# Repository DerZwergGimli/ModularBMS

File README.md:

## Battery Management System [BMS]

This is a Bachelor Project made at the HTWG.

This Project is about a Battery Management System - build as a scale-able system.

## Boards

### Master

#### - Battery Management System [BMS]

### Slaves

#### - Battery Monitoring Unit [BMU]

#### - Battery Junction Box [BJB]

### Extra

#### - 6 Cell Battery Simulator [6CBS]

### 

### 

### 

###

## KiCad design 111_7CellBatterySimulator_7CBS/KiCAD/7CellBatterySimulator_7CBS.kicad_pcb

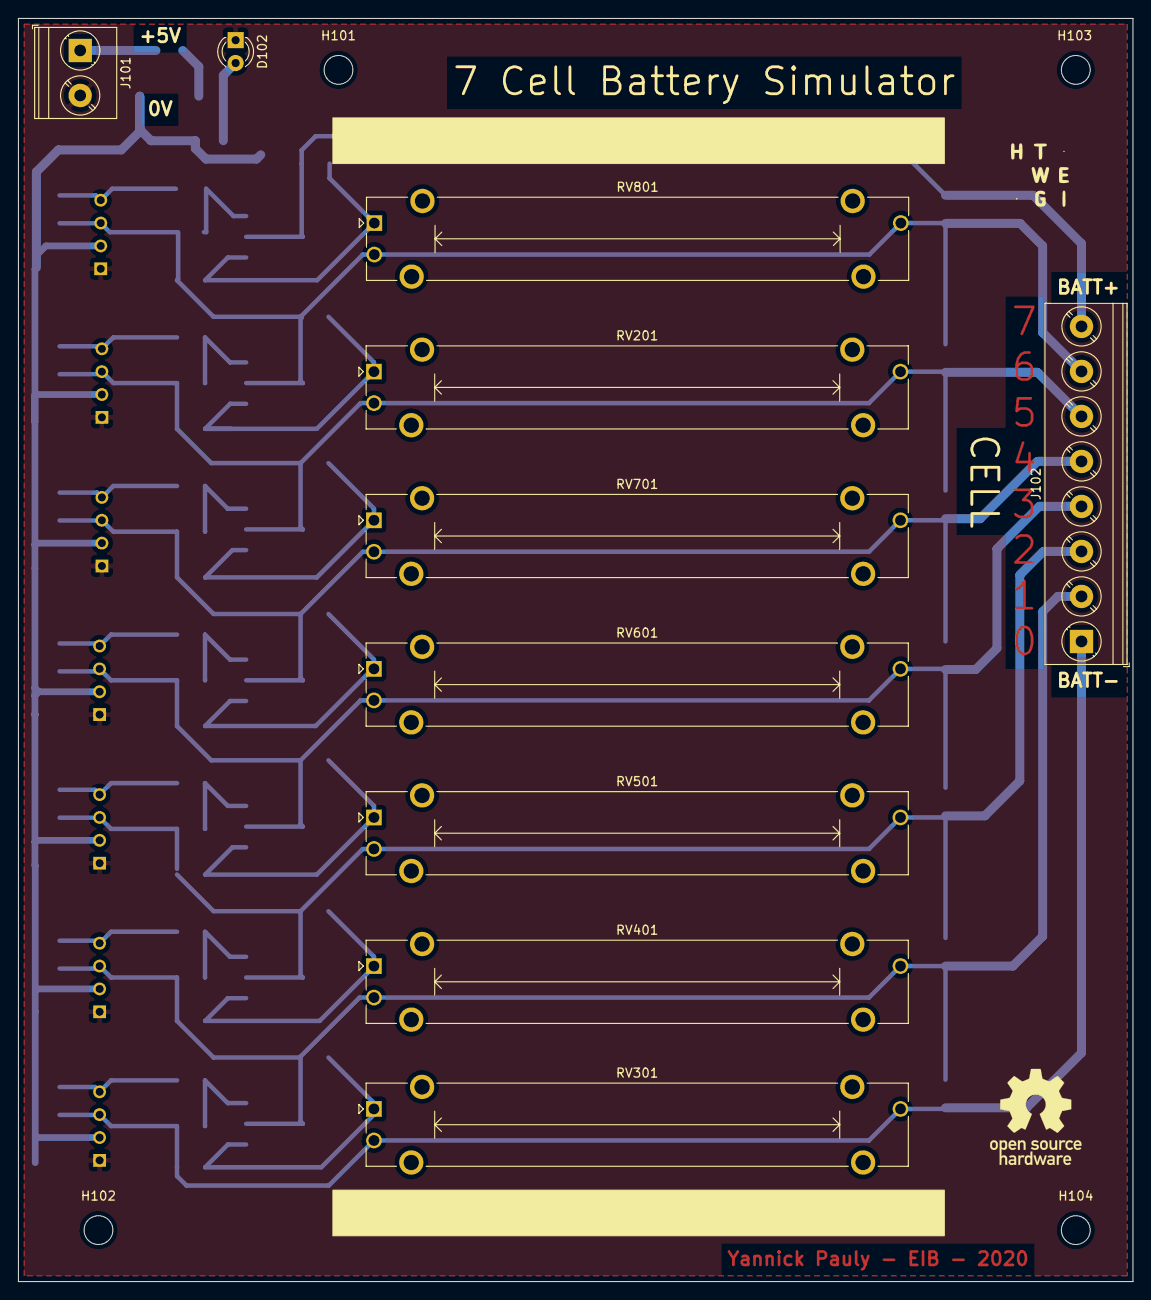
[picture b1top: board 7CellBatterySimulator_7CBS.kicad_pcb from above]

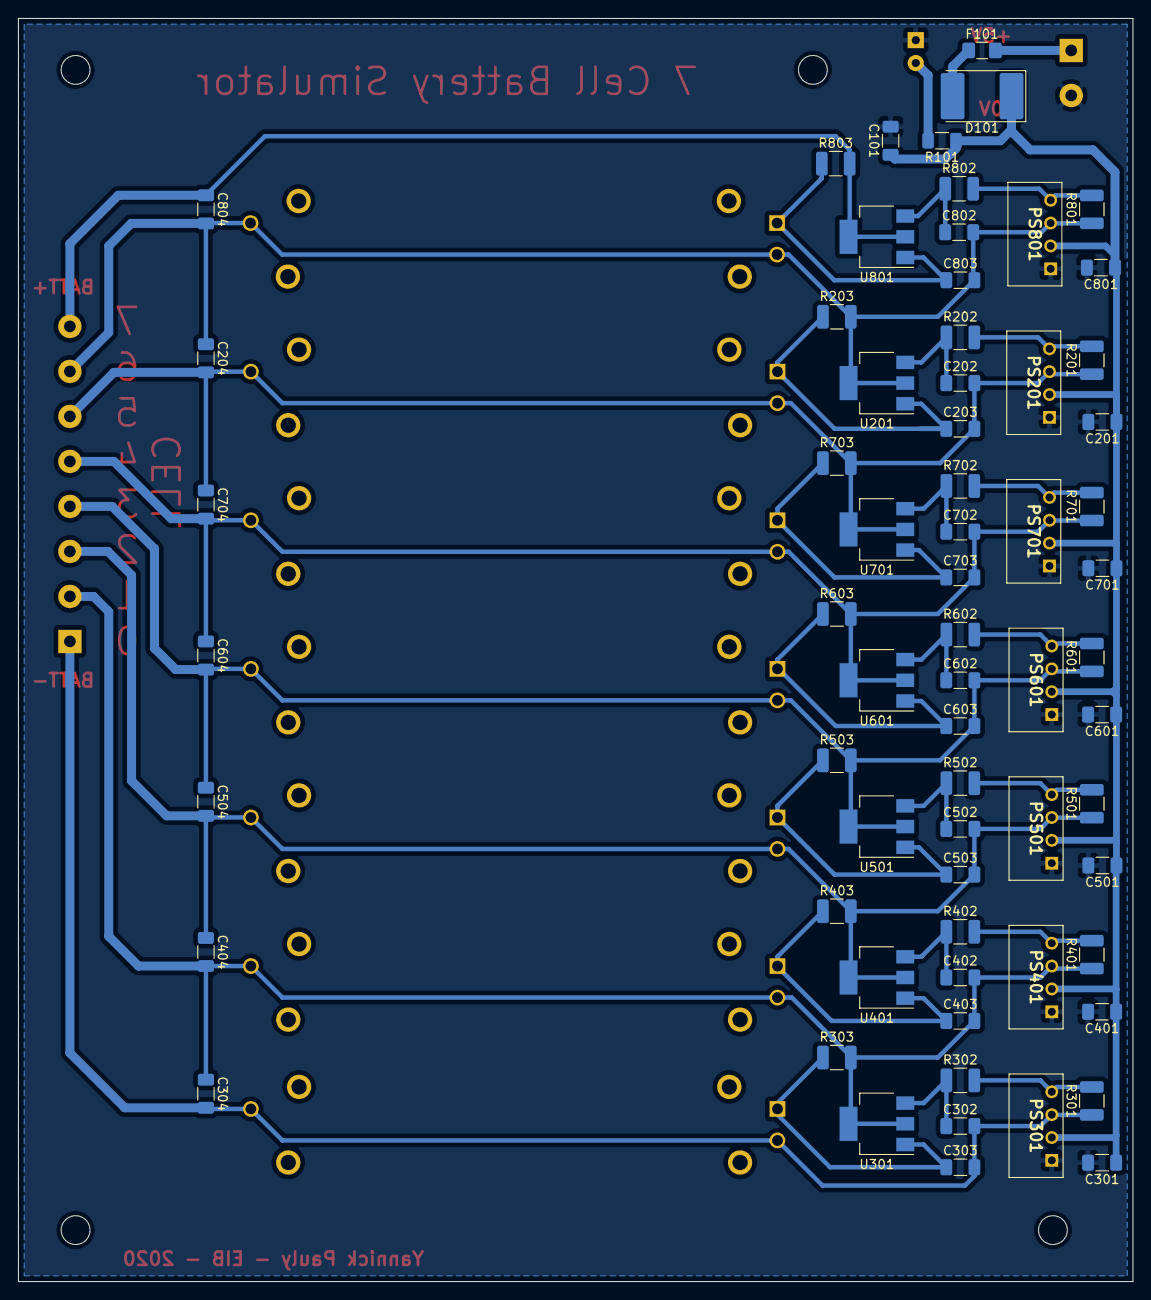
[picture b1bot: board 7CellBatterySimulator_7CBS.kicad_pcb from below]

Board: 2 copper layers, 123.8 x 140.3 mm, 83 parts (67 on the bottom side), 34 nets.

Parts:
C101: 47u; C_1206_3216Metric_Pad1.33x1.80mm_HandSolder
C201, C301, C401, C501, C601, C701, C801: 10u*; C_1206_3216Metric_Pad1.33x1.80mm_HandSolder
C202, C302, C402, C502, C602, C702, C802: 0.1u*; C_1206_3216Metric_Pad1.33x1.80mm_HandSolder
C203, C303, C403, C503, C603, C703, C803: 1u*; C_1206_3216Metric_Pad1.33x1.80mm_HandSolder
C204, C304, C404, C504, C604, C704, C804: 100u; C_1206_3216Metric_Pad1.33x1.80mm_HandSolder
D101: 60V; D_3220_8050Metric_Pad2.65x5.15mm_HandSolder
D102: LED; LED_D3.0mm
F101: 4A; Fuse_1206_3216Metric_Pad1.42x1.75mm_HandSolder
H101, H102, H103, H104: MountingHole; MountingHole_3.2mm_M3_DIN965
J101: Screw_Terminal_01x02; TerminalBlock_Phoenix_PT-1,5-2-5.0-H_1x02_P5.00mm_Horizontal
J102: Screw_Terminal_01x08; TerminalBlock_Phoenix_PT-1,5-8-5.0-H_1x08_P5.00mm_Horizontal
L101: LogoHTWG; HTWG_LOGO
L102: LogoOSH; OpenSouceHardwareLOGO
PS201, PS301, PS401, PS501, PS601, PS701, PS801: ROE-0512S; ROE1205S
R101: 330; R_1206_3216Metric_Pad1.30x1.75mm_HandSolder
R201, R301, R401, R501, R601, R701, R801: 1k, DNP; R_1210_3225Metric_Pad1.30x2.65mm_HandSolder
R202, R302, R402, R502, R602, R702, R802: 22; R_1210_3225Metric_Pad1.30x2.65mm_HandSolder
R203, R303, R403, R503, R603, R703, R803: 380; R_1210_3225Metric_Pad1.30x2.65mm_HandSolder
RV201, RV301, RV401, RV501, RV601, RV701, RV801: 1k; Potentiometer_Bourns_PTA4543_Single_Slide
U201, U301, U401, U501, U601, U701, U801: LM317_SOT-223; SOT-223-3_TabPin2

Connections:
+5V: C101.1, C201.1, C301.1, C401.1, C501.1, C601.1, C701.1, C801.1, D101.1, PS201.2, PS301.2, PS401.2, PS501.2, PS601.2, PS701.2, PS801.2, R101.1
/Channel1/OUT+: C304.1, C402.2, C403.2, C404.2, J102.2, PS401.3, R303.2, R401.1, RV401.2, RV401.3, U301.2
/Channel1/OUT-: C302.2, C303.2, C304.2, J102.1, PS301.3, R301.1, RV301.2, RV301.3
/Channel2/OUT+: C404.1, C502.2, C503.2, C504.2, J102.3, PS501.3, R403.2, R501.1, RV501.2, RV501.3, U401.2
/Channel3/OUT+: C504.1, C602.2, C603.2, C604.2, J102.4, PS601.3, R503.2, R601.1, RV601.2, RV601.3, U501.2
/Channel4/OUT+: C604.1, C702.2, C703.2, C704.2, J102.5, PS701.3, R603.2, R701.1, RV701.2, RV701.3, U601.2
/Channel5/OUT+: C202.2, C203.2, C204.2, C704.1, J102.6, PS201.3, R201.1, R703.2, RV201.2, RV201.3, U701.2
/Channel6/OUT+: C204.1, C802.2, C803.2, C804.2, J102.7, PS801.3, R203.2, R801.1, RV801.2, RV801.3, U201.2
/Channel7/OUT+: C804.1, J102.8, R803.2, U801.2
GND: C101.2, C201.2, C301.2, C401.2, C501.2, C601.2, C701.2, C801.2, D102.1, J101.2, PS201.1, PS301.1, PS401.1, PS501.1, PS601.1, PS701.1, PS801.1
unnamed: C202.1, R202.1, U201.3
unnamed: C203.1, R203.1, RV201.1, U201.1
unnamed: C302.1, R302.1, U301.3
unnamed: C303.1, R303.1, RV301.1, U301.1
unnamed: C402.1, R402.1, U401.3
unnamed: C403.1, R403.1, RV401.1, U401.1
unnamed: C502.1, R502.1, U501.3
unnamed: C503.1, R503.1, RV501.1, U501.1
unnamed: C602.1, R602.1, U601.3
unnamed: C603.1, R603.1, RV601.1, U601.1
unnamed: C702.1, R702.1, U701.3
unnamed: C703.1, R703.1, RV701.1, U701.1
unnamed: C802.1, R802.1, U801.3
unnamed: C803.1, R803.1, RV801.1, U801.1
unnamed: D101.2, F101.1
unnamed: D102.2, R101.2
unnamed: F101.2, J101.1
unnamed: PS201.4, R201.2, R202.2
unnamed: PS301.4, R301.2, R302.2
unnamed: PS401.4, R401.2, R402.2
unnamed: PS501.4, R501.2, R502.2
unnamed: PS601.4, R601.2, R602.2
unnamed: PS701.4, R701.2, R702.2
unnamed: PS801.4, R801.2, R802.2

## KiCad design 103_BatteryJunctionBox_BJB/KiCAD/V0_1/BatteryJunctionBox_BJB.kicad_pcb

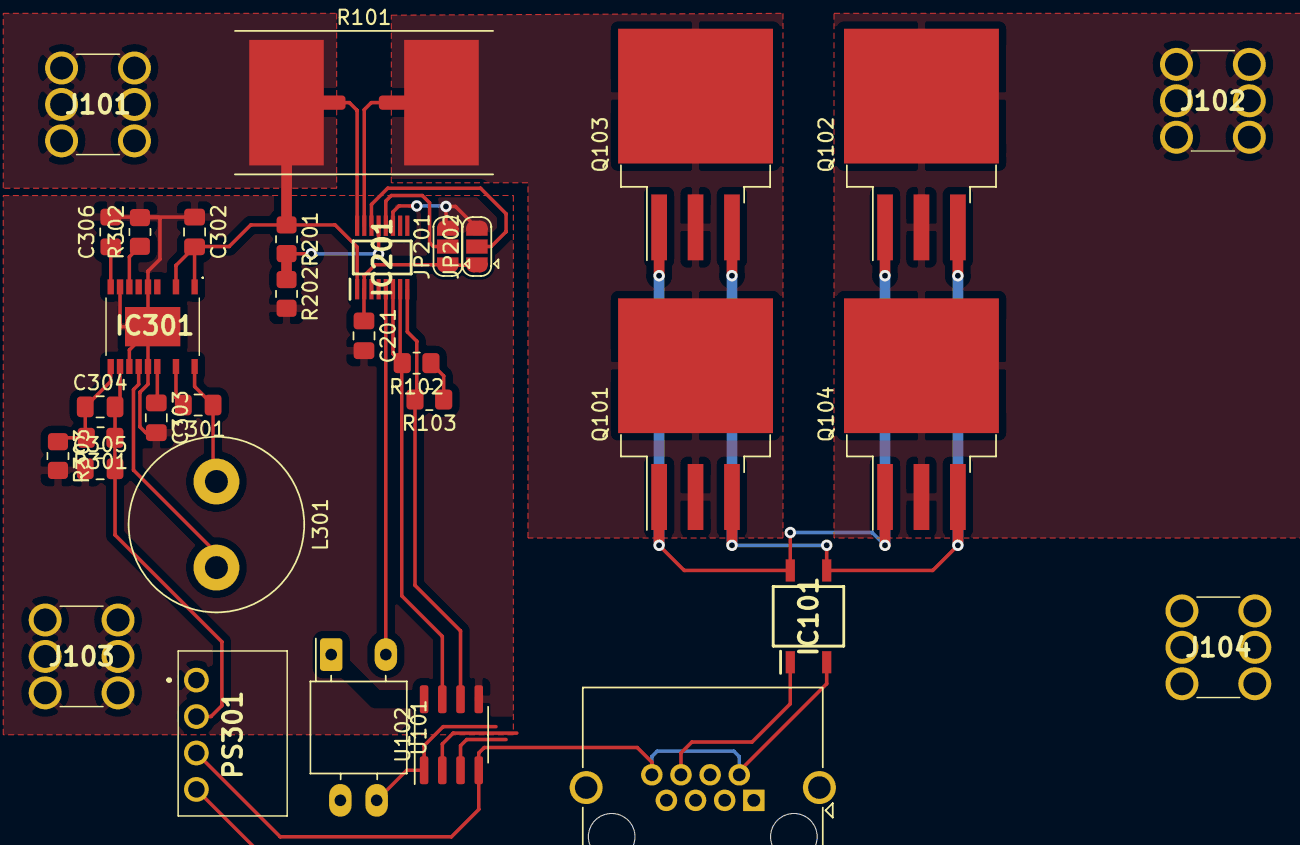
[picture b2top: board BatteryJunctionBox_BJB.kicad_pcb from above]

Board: 2 copper layers, 33 parts (0 on the bottom side), 30 nets.

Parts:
C201, C301, C306: 0.1u; C_0805_2012Metric_Pad1.18x1.45mm_HandSolder
C302, C303: 2.2u; C_0805_2012Metric_Pad1.18x1.45mm_HandSolder
C304: 10p; C_0805_2012Metric_Pad1.18x1.45mm_HandSolder
C305: 47u; C_0805_2012Metric_Pad1.18x1.45mm_HandSolder
IC101: VOM1271T; SOP-4
IC201: LTC2946; MSOP_16_Lead_Plastic
IC301: LT8630IFE#PBF; LT8630IFEPBF
J101, J102, J103, J104: WuertHA_7461057
J105: RJ45_Shielded; RJ45_Amphenol_RJHSE5380
JP201, JP202: Jumper_3_Open; SolderJumper-3_P1.3mm_Open_RoundedPad1.0x1.5mm
L301: 22u; L_Radial_D12.0mm_P6.00mm_MuRATA_1900R
PS301: RI-1205S; SIP4_SingleOutput
Q101, Q102, Q103, Q104: Q_NMOS_GDS; TO-263-3_TabPin2
R101: 0.001; R_Shunt_16x8-75_Bourns_4Pin
R102, R103: 10k; R_0805_2012Metric_Pad1.20x1.40mm_HandSolder
R201, R301: 1Mega; R_0805_2012Metric_Pad1.20x1.40mm_HandSolder
R202: 20k; R_0805_2012Metric_Pad1.20x1.40mm_HandSolder
R302: 8.66k; R_0805_2012Metric_Pad1.20x1.40mm_HandSolder
R303: 71.5k; R_0805_2012Metric_Pad1.20x1.40mm_HandSolder
U101: NSL-32; Luna_NSL-32
U102: ISO1541; SOIC-8_3.9x4.9mm_P1.27mm

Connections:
+3V3: J105.7, U101.3, U102.1
+5V: C201.1, IC201.2, JP201.1, JP202.1, R102.1, R103.1, U101.1, U102.8
+BATT: C302.2, IC201.1, IC301.1, IC301.3, J101.1, J101.2, J101.3, J101.4, J101.5, J101.6, R101.1, R201.1
-BATT: C201.2, C302.1, C303.2, C305.1, C306.2, IC201.11, IC301.6, IC301.9, IC301.13, IC301.15, IC301.21, J103.1, J103.2, J103.3, J103.4, J103.5, J103.6, J104.1, J104.2, J104.3, J104.4, J104.5, J104.6, JP201.3, JP202.3, PS301.1, R202.2, R302.2, R303.2, U102.5
/IsoPowerSupply/12V_OUT: C304.2, C305.2, IC301.12, PS301.2, R301.1
/PowerMonitor/ADIN: IC201.13, R201.2, R202.1
/PowerMonitor/Address0: IC201.12, JP201.2
/PowerMonitor/Address1: IC201.14, JP202.2
I2C_SCL: IC201.8, R103.2, U102.6
I2C_SCL_ISO: J105.4, U102.3
I2C_SDA: IC201.6, IC201.7, R102.2, U102.7
I2C_SDA_ISO: J105.3, U102.2
ISO_+5V: J105.1, PS301.4
ISO_GND: IC101.2, J105.2, J105.8, PS301.3, U102.4
Interrupt_NO: J105.5, U101.4
MOSFET_G: IC101.4, Q101.1, Q102.1, Q103.1, Q104.1
MOSFET_S: IC101.3, Q101.3, Q102.3, Q103.3, Q104.3
MOSFET_SWITCH: IC101.1, J105.6
unnamed: C301.1, IC301.20, L301.1
unnamed: C301.2, IC301.18
unnamed: C303.1, IC301.16
unnamed: C304.1, IC301.11, R301.2, R303.1
unnamed: C306.1, IC301.10
unnamed: IC301.8, R302.1
unnamed: IC301.14, L301.2
unnamed: J102.1, J102.2, J102.3, J102.4, J102.5, J102.6, Q102.2, Q104.2
unnamed: Q101.2, Q103.2, R101.4
SHUNT+: IC201.16, R101.2
SHUNT-: IC201.15, R101.3
~ALERT: IC201.5, U101.2

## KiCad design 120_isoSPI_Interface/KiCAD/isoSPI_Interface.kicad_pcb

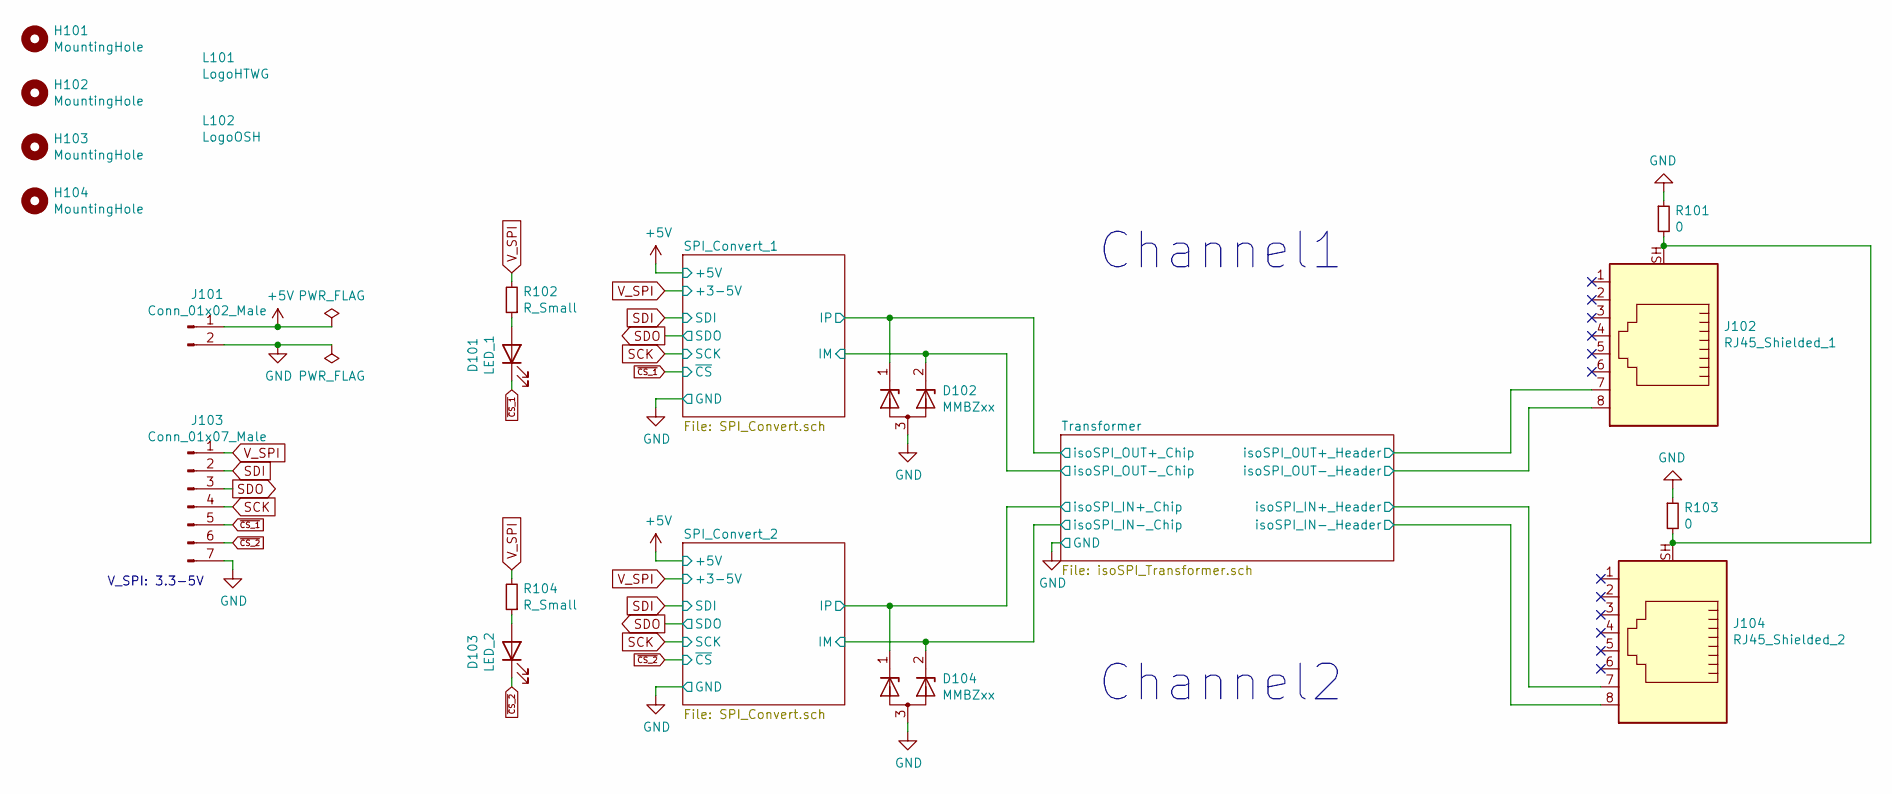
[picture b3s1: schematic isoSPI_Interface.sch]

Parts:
D101: LED_1; LED_D3.0mm
D102, D104: MMBZxx; SOT-23
D103: LED_2; LED_D3.0mm
H101, H102, H103, H104: MountingHole; MountingHole_3.2mm_M3_DIN965
J101: Conn_01x02_Male; PinHeader_1x02_P2.54mm_Vertical
J102: RJ45_Shielded_1; RJ45_Amphenol_RJHSE5380
J103: Conn_01x07_Male; PinHeader_1x07_P2.54mm_Vertical
J104: RJ45_Shielded_2; RJ45_Amphenol_RJHSE5380
L101: LogoHTWG; HTWG_LOGO
L102: LogoOSH; OpenSouceHardwareLOGO
R101, R103: 0; R_0805_2012Metric_Pad1.20x1.40mm_HandSolder
R102, R104: R_Small; R_0805_2012Metric_Pad1.20x1.40mm_HandSolder

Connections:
+5V: J101.1; also elsewhere on the board
/SPI_Convert_1/IM: D102.2 (K); also elsewhere on the board
/SPI_Convert_1/IP: D102.1 (K); also elsewhere on the board
/SPI_Convert_2/IM: D104.2 (K); also elsewhere on the board
/SPI_Convert_2/IP: D104.1 (K); also elsewhere on the board
/Transformer/isoSPI_IN+_Header: J104.7; also elsewhere on the board
/Transformer/isoSPI_IN-_Header: J104.8; also elsewhere on the board
/Transformer/isoSPI_OUT+_Header: J102.7; also elsewhere on the board
/Transformer/isoSPI_OUT-_Header: J102.8; also elsewhere on the board
GND: D102.3 (A), D104.3 (A), J101.2, J103.7, R101.1, R103.1; also elsewhere on the board
unnamed: D101.2 (A), R102.1
unnamed: D103.2 (A), R104.1
unnamed: J102.SH, J104.SH, R101.2, R103.2
SCK: J103.4; also elsewhere on the board
SDI: J103.2; also elsewhere on the board
SDO: J103.3; also elsewhere on the board
V_SPI: J103.1, R102.2, R104.2; also elsewhere on the board
~CS_1: D101.1 (K), J103.5; also elsewhere on the board
~CS_2: D103.1 (K), J103.6; also elsewhere on the board

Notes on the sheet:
V_SPI: 3.3-5V
Channel1
Channel2

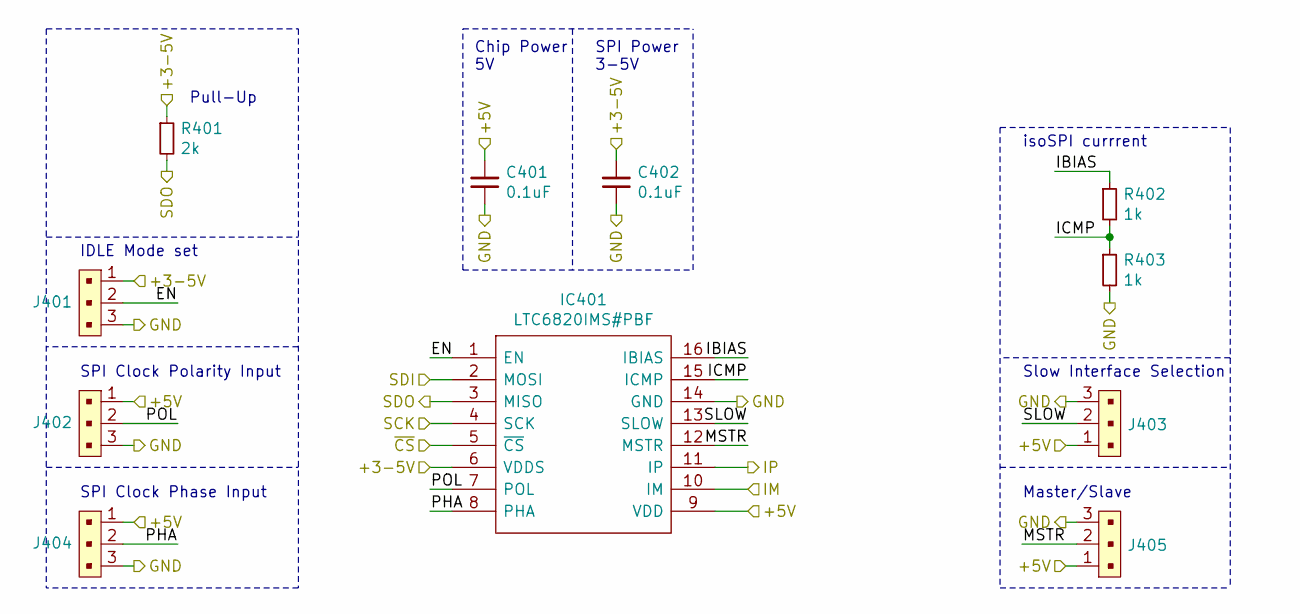
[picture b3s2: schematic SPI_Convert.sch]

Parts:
C201, C202: 0.1uF; C_0805_2012Metric_Pad1.18x1.45mm_HandSolder
IC201: LTC6820IMS#PBF; MSOP-16_3x4.039mm_P0.5mm
J201, J202, J203, J204, J205: 3PinHeader; PinHeader_1x03_P2.54mm_Vertical; MPN 640456-3; Digi-Key_PN A19470-ND
R201: 2k; R_0805_2012Metric_Pad1.20x1.40mm_HandSolder
R202, R203: 1k; R_0805_2012Metric_Pad1.20x1.40mm_HandSolder

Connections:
+5V: C201.2, IC201.9 (VDD), J202.1, J203.1, J204.1, J205.1; also elsewhere on the board
/SPI_Convert_1/EN: IC201.1 (EN), J201.2
/SPI_Convert_1/IBIAS: IC201.16 (IBIAS), R202.1
/SPI_Convert_1/ICMP: IC201.15 (ICMP), R202.2, R203.1
/SPI_Convert_1/IM: IC201.10 (IM); also elsewhere on the board
/SPI_Convert_1/IP: IC201.11 (IP); also elsewhere on the board
/SPI_Convert_1/MSTR: IC201.12 (MSTR), J205.2
/SPI_Convert_1/PHA: IC201.8 (PHA), J204.2
/SPI_Convert_1/POL: IC201.7 (POL), J202.2
/SPI_Convert_1/SLOW: IC201.13 (SLOW), J203.2
GND: C201.1, C202.1, IC201.14 (GND), J201.3, J202.3, J203.3, J204.3, J205.3, R203.2; also elsewhere on the board
SCK: IC201.4 (SCK); also elsewhere on the board
SDI: IC201.2 (MOSI); also elsewhere on the board
SDO: IC201.3 (MISO), R201.2; also elsewhere on the board
V_SPI: C202.2, IC201.6 (VDDS), J201.1, R201.1; also elsewhere on the board
~CS_1: IC201.5 (~CS); also elsewhere on the board

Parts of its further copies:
C401, C402: 0.1uF; C_0805_2012Metric_Pad1.18x1.45mm_HandSolder
IC401: LTC6820IMS#PBF; MSOP-16_3x4.039mm_P0.5mm
J401, J402, J403, J404, J405: 3PinHeader; PinHeader_1x03_P2.54mm_Vertical; MPN 640456-3; Digi-Key_PN A19470-ND
R401: 2k; R_0805_2012Metric_Pad1.20x1.40mm_HandSolder
R402, R403: 1k; R_0805_2012Metric_Pad1.20x1.40mm_HandSolder

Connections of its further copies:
+5V: C401.2, IC401.9 (VDD), J402.1, J403.1, J404.1, J405.1; also elsewhere on the board
/SPI_Convert_2/EN: IC401.1 (EN), J401.2
/SPI_Convert_2/IBIAS: IC401.16 (IBIAS), R402.1
/SPI_Convert_2/ICMP: IC401.15 (ICMP), R402.2, R403.1
/SPI_Convert_2/IM: IC401.10 (IM); also elsewhere on the board
/SPI_Convert_2/IP: IC401.11 (IP); also elsewhere on the board
/SPI_Convert_2/MSTR: IC401.12 (MSTR), J405.2
/SPI_Convert_2/PHA: IC401.8 (PHA), J404.2
/SPI_Convert_2/POL: IC401.7 (POL), J402.2
/SPI_Convert_2/SLOW: IC401.13 (SLOW), J403.2
GND: C401.1, C402.1, IC401.14 (GND), J401.3, J402.3, J403.3, J404.3, J405.3, R403.2; also elsewhere on the board
SCK: IC401.4 (SCK); also elsewhere on the board
SDI: IC401.2 (MOSI); also elsewhere on the board
SDO: IC401.3 (MISO), R401.2; also elsewhere on the board
V_SPI: C402.2, IC401.6 (VDDS), J401.1, R401.1; also elsewhere on the board
~CS_2: IC401.5 (~CS); also elsewhere on the board

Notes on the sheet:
Master/Slave
Slow Interface Selection
Chip Power 5V
SPI Power 3-5V
SPI Clock Polarity Input
SPI Clock Phase Input
IDLE Mode set
Pull-Up
isoSPI currrent

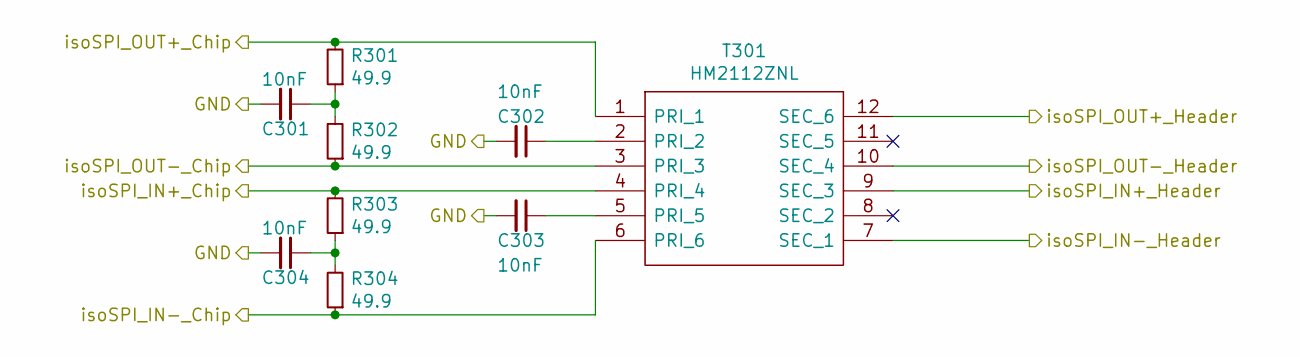
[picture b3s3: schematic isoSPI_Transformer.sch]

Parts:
C301, C302, C303, C304: 10nF; C_0805_2012Metric_Pad1.18x1.45mm_HandSolder
R301, R302, R303, R304: 49.9; R_0805_2012Metric_Pad1.20x1.40mm_HandSolder
T301: HM2112ZNL; SOP200P1543X320-12N; Manufacturer_Part_Number HM2112ZNL; Mouser Part Number 673-HM2112ZNL

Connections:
/SPI_Convert_1/IM: R302.1, T301.3 (PRI_3); also elsewhere on the board
/SPI_Convert_1/IP: R301.2, T301.1 (PRI_1); also elsewhere on the board
/SPI_Convert_2/IM: R304.1, T301.6 (PRI_6); also elsewhere on the board
/SPI_Convert_2/IP: R303.2, T301.4 (PRI_4); also elsewhere on the board
/Transformer/isoSPI_IN+_Header: T301.9 (SEC_3); also elsewhere on the board
/Transformer/isoSPI_IN-_Header: T301.7 (SEC_1); also elsewhere on the board
/Transformer/isoSPI_OUT+_Header: T301.12 (SEC_6); also elsewhere on the board
/Transformer/isoSPI_OUT-_Header: T301.10 (SEC_4); also elsewhere on the board
GND: C301.2, C302.2, C303.2, C304.2; also elsewhere on the board
unnamed: C301.1, R301.1, R302.2
unnamed: C302.1, T301.2 (PRI_2)
unnamed: C303.1, T301.5 (PRI_5)
unnamed: C304.1, R303.1, R304.2

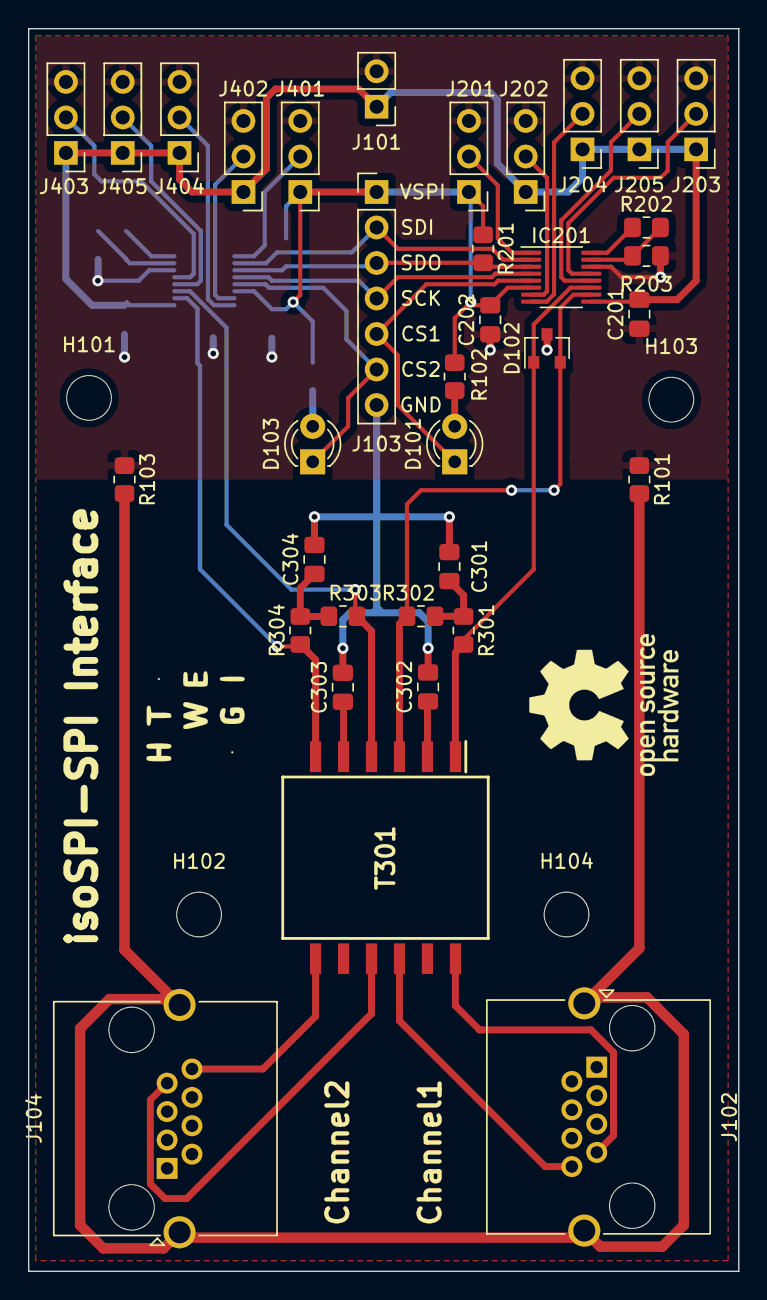
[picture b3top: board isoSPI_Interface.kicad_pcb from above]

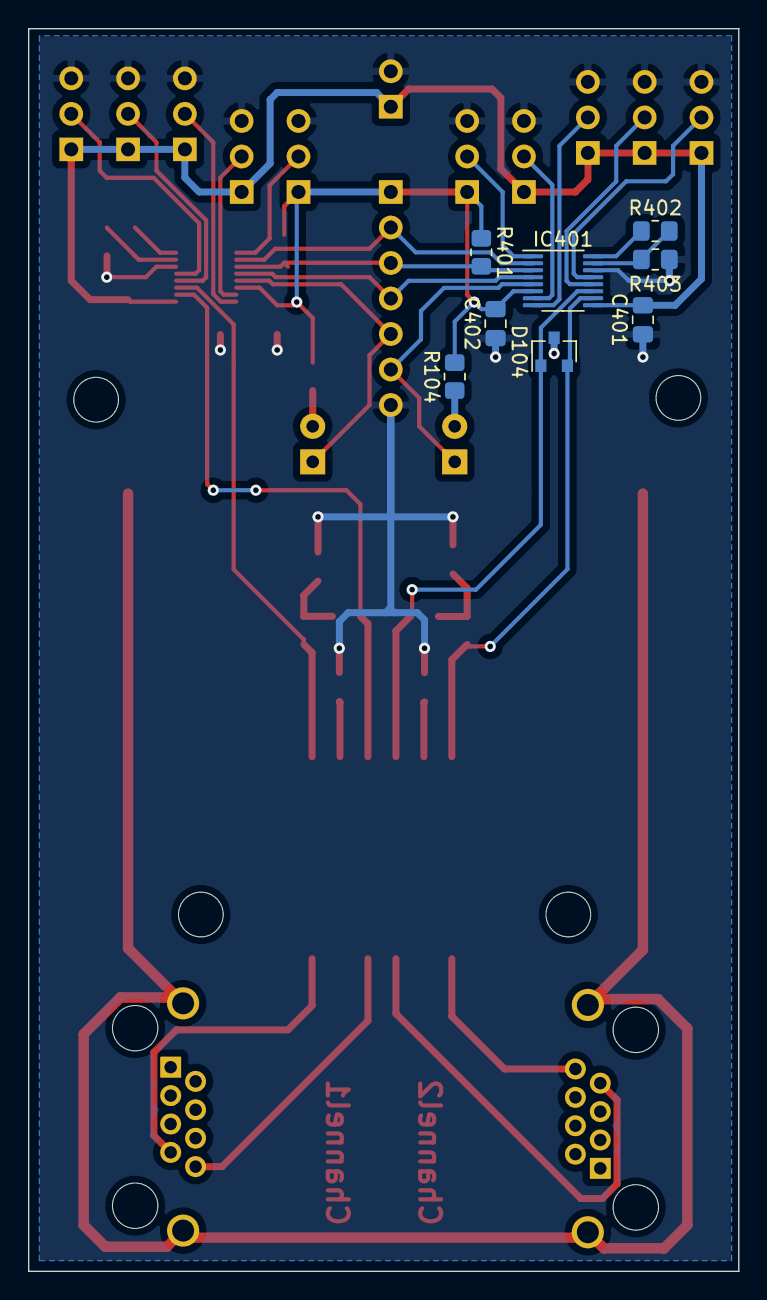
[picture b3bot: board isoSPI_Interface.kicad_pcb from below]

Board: 2 copper layers, 50.8 x 88.9 mm, 49 parts (8 on the bottom side), 37 nets.

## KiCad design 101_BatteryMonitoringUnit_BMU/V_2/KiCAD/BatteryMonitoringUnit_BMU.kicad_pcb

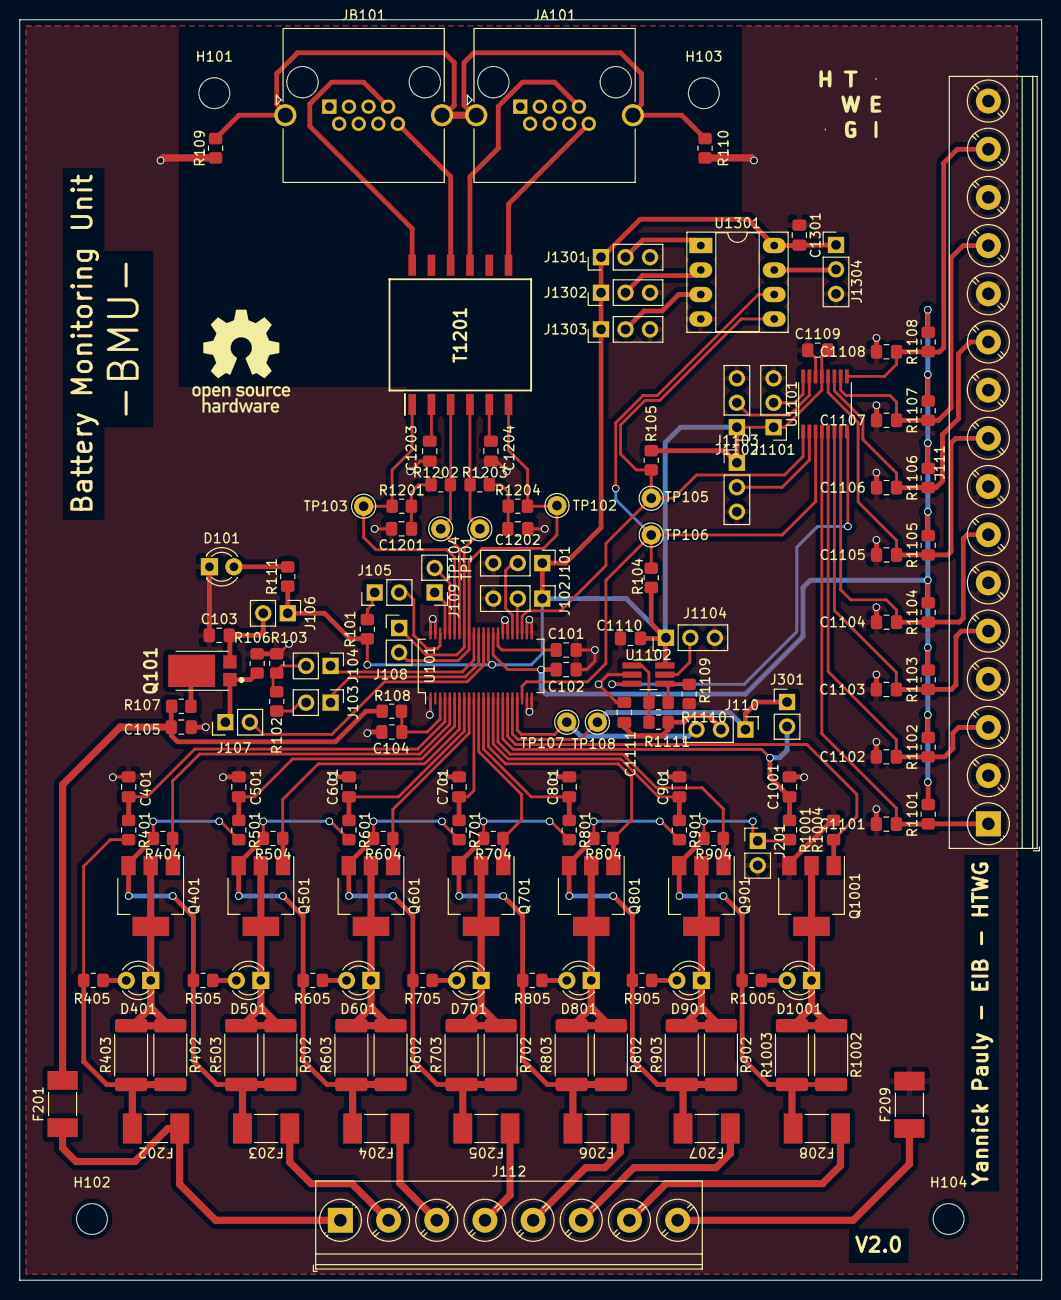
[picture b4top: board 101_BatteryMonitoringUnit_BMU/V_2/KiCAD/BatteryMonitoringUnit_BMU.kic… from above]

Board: 2 copper layers, 106.0 x 130.8 mm, 157 parts (0 on the bottom side), 101 nets.

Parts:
C101, C102, C103: 1uF; C_0805_2012Metric_Pad1.18x1.45mm_HandSolder
C104, C1111, C1201, C1202, C1203, C1204: 10nF; C_0805_2012Metric_Pad1.18x1.45mm_HandSolder
C105, C1110: 0.1u; C_0805_2012Metric_Pad1.18x1.45mm_HandSolder
C401, C501, C601, C701, C801, C901, C1001: 10nF/30V; C_0805_2012Metric_Pad1.18x1.45mm_HandSolder
C1101, C1102, C1103, C1104, C1105, C1106, C1107, C1108: 10nF*; C_0805_2012Metric_Pad1.18x1.45mm_HandSolder
C1109, C1301: 100nF; C_0805_2012Metric_Pad1.18x1.45mm_HandSolder
D101: LED_Status; LED_D3.0mm
D401, D501, D601, D701, D801, D901, D1001: LED_Dis; LED_D3.0mm
F201, F209: Fuse_0.5A; Fuse_Littelfuse-NANO2-451_453
F202, F203, F204, F205, F206, F207, F208: Fuse_0.25A; Fuse_Littelfuse-NANO2-451_453
H101, H102, H103, H104: MountingHole; MountingHole_3.2mm_M3_DIN965
J101, J102, J110, J1101, J1102, J1103, J1104, J1301, J1302, J1303, J1304: 3PinHeader; PinHeader_1x03_P2.54mm_Vertical
J103, J104, J105, J106, J107, J108, J109, J201, J301: 2PinHeader; PinHeader_1x02_P2.54mm_Vertical
J111: TerminalBlock; TerminalBlock_Phoenix_PT-1,5-16-5.0-H_1x16_P5.00mm_Horizont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
J112: Screw_Terminal_01x08; TerminalBlock_Phoenix_PT-1,5-8-5.0-H_1x08_P5.00mm_Horizontal
JA101: RJ45; RJ45_Amphenol_RJHSE5380
JB101: RJ45; RJ45_Amphenol_RJHSE5380
L101: LogoHTWG; HTWG_LOGO
L102: LogoOSH; OpenSouceHardwareLOGO
Q101: DXT5551P5-13; DXT5551P513
Q401, Q501, Q601, Q701, Q801, Q901, Q1001: PZT2222A; SOT-223-3_TabPin2
R101: 1M; R_0805_2012Metric_Pad1.20x1.40mm_HandSolder
R102, R103, R404, R504, R604, R704, R804, R904, R1004: 1k; R_0805_2012Metric_Pad1.20x1.40mm_HandSolder
R104, R105, R1101, R1102, R1103, R1104, R1105, R1106, R1107, R1108, R1109: 10k; R_0805_2012Metric_Pad1.20x1.40mm_HandSolder
R106: 1k, DNP; R_0805_2012Metric_Pad1.20x1.40mm_HandSolder
R107, R109, R110, R1110: 0; R_0805_2012Metric_Pad1.20x1.40mm_HandSolder
R108: 10; R_0805_2012Metric_Pad1.20x1.40mm_HandSolder
R111, R405, R505, R605, R705, R805, R905, R1005: Rv_LED; R_0805_2012Metric_Pad1.20x1.40mm_HandSolder
R401, R501, R601, R701, R801, R901, R1001, R1111: 100; R_0805_2012Metric_Pad1.20x1.40mm_HandSolder
R402, R403, R502, R503, R602, R603, R702, R703, R802, R803, R902, R903, R1002, R1003: 100; R_2512_6332Metric_Pad1.40x3.35mm_HandSolder
R1201, R1202, R1203, R1204: 49.9; R_0805_2012Metric_Pad1.20x1.40mm_HandSolder
T1201: HM2112ZNL; SOP200P1543X320-12N
TP101, TP102, TP103, TP104, TP105, TP106, TP107, TP108: TestPoint; Pin_D1.0mm_L10.0mm
U101: LTC6810-1_mod; SSOP-44_5.3x12.8mm_P0.5mm
U1101: ADG728; TSSOP-16_4.4x5mm_P0.65mm
U1102: LTC6255; TSOT-23-6_HandSoldering
U1301: 24LC256; DIP-8_W7.62mm_Socket_LongPads

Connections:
+BATT: F201.1, F202.1, J112.1
+BATT_Fused: C105.2, F201.2, R107.1, R108.2
-BATT: F209.1, J112.8
-BATT_Fused: C101.2, C102.2, C103.1, C104.1, C105.1, C401.2, C501.2, C601.2, C701.2, C801.2, C901.2, C1001.2, C1101.2, C1102.2, C1103.2, C1104.2, C1105.2, C1106.2, C1107.2, C1108.2, C1109.1, C1110.2, C1111.2, C1201.2, C1202.2, C1203.2, C1204.1, C1301.1, D101.1, F209.2, J101.3, J102.3, J111.2, J111.4, J111.6, J111.8, J111.10, J111.12, J111.14, J111.16, J201.2, J1101.3, J1102.3, J1103.3, J1104.3, J1301.3, J1302.3, J1303.3, J1304.3, Q1001.3, R103.1, R106.2, R109.1, R110.1, R1004.2, R1109.2, U101.1, U101.21, U101.22, U101.23, U101.24, U101.28, U101.29, U101.43, U101.44, U1101.14, U1102.2, U1301.4
/+Cell_0: F208.1, J112.7
/+Cell_1: F207.1, J112.6
/+Cell_2: F206.1, J112.5
/+Cell_3: F205.1, J112.4
/+Cell_4: F204.1, J112.3
/+Cell_5: F203.1, J112.2
/BalanceFuses/+FusedCell_0: F208.2, J201.1, Q901.3, R904.2, R1001.2, R1002.2, R1003.1, R1005.1
/BalanceFuses/+FusedCell_1: F207.2, Q801.3, R804.2, R901.2, R902.2, R903.1, R905.1
/BalanceFuses/+FusedCell_2: F206.2, Q701.3, R704.2, R801.2, R802.2, R803.1, R805.1
/BalanceFuses/+FusedCell_3: F205.2, Q601.3, R604.2, R701.2, R702.2, R703.1, R705.1
/BalanceFuses/+FusedCell_4: F204.2, Q501.3, R504.2, R601.2, R602.2, R603.1, R605.1
/BalanceFuses/+FusedCell_5: F203.2, Q401.3, R404.2, R501.2, R502.2, R503.1, R505.1
/BalanceFuses/+FusedCell_6: F202.2, R401.2, R402.2, R403.1, R405.1
/C_0: C1001.1, J301.2, R1001.1, U101.16
/C_1: C901.1, R901.1, U101.14
/C_2: C801.1, R801.1, U101.12
/C_3: C701.1, R701.1, U101.10
/C_4: C601.1, R601.1, U101.8
/C_5: C501.1, R501.1, U101.6
/C_6: C401.1, R401.1, U101.4
/MUX_I2C/A0: J1101.2, U1101.16
/MUX_I2C/A1: J1102.2, U1101.15
/MUX_I2C/TempData: C1111.1, J110.2, R1111.2
/MUX_I2C/~RESET: J1103.2, U1101.2
/MUX_I2C/~SHDN: J1104.2, U1102.5
/NTC_0: C1101.1, J111.1, R1101.1, U1101.4
/NTC_1: C1102.1, J111.3, R1102.1, U1101.5
/NTC_2: C1103.1, J111.5, R1103.1, U1101.6
/NTC_3: C1104.1, J111.7, R1104.1, U1101.7
/NTC_4: C1105.1, J111.9, R1105.1, U1101.12
/NTC_5: C1106.1, J111.11, R1106.1, U1101.11
/NTC_6: C1107.1, J111.13, R1107.1, U1101.10
/NTC_7: C1108.1, J111.15, R1108.1, U1101.9
/S_0: Q1001.1, R1004.1, U101.17
/S_1: Q901.1, R904.1, U101.15
/S_2: Q801.1, R804.1, U101.13
/S_3: Q701.1, R704.1, U101.11
/S_4: Q601.1, R604.1, U101.9
/S_5: Q501.1, R504.1, U101.7
/S_6: Q401.1, R404.1, U101.5
/isoSPI/isoSPI_IN+_Header: JA101.7, T1201.9
/isoSPI/isoSPI_IN-_Header: JA101.8, T1201.7
/isoSPI/isoSPI_OUT+_Header: JB101.7, T1201.12
/isoSPI/isoSPI_OUT-_Header: JB101.8, T1201.10
/sheet5FB9F446/A0: J1301.2, U1301.1
/sheet5FB9F446/A1: J1302.2, U1301.2
/sheet5FB9F446/A2: J1303.2, U1301.3
/sheet5FB9F446/~ENABLE: J1304.2, U1301.7
DRIVE: J107.2, U101.33
DTEN: J102.2, U101.26
GPIO1_(ADC): J110.1, J301.1, TP108.1, U101.18
GPIO2_(ADC): J110.3, TP107.1, U101.19
GPIO3_(SDA): R104.1, TP106.1, U101.20, U1101.3, U1301.6
GPIO4_(SCL): R105.1, TP105.1, U101.25, U1101.1, U1301.5
IBIAS: J103.1, U101.34
ICMP: J104.1, U101.35
ISOMD: J101.2, U101.27
unnamed: C103.2, J106.2, Q101.2
unnamed: C104.2, R108.1, U101.3
unnamed: C1201.1, R1201.2, R1202.1
unnamed: C1202.1, R1203.2, R1204.1
unnamed: C1203.1, T1201.2
unnamed: C1204.2, T1201.5
unnamed: D101.2, R111.2
unnamed: D401.1, Q401.2, R402.1, R403.2
unnamed: D401.2, R405.2
unnamed: D501.1, Q501.2, R502.1, R503.2
unnamed: D501.2, R505.2
unnamed: D601.1, Q601.2, R602.1, R603.2
unnamed: D601.2, R605.2
unnamed: D701.1, Q701.2, R702.1, R703.2
unnamed: D701.2, R705.2
unnamed: D801.1, Q801.2, R802.1, R803.2
unnamed: D801.2, R805.2
unnamed: D901.1, Q901.2, R902.1, R903.2
unnamed: D901.2, R905.2
unnamed: D1001.1, Q1001.2, R1002.1, R1003.2
unnamed: D1001.2, R1005.2
unnamed: J103.2, R102.2
unnamed: J104.2, R102.1, R103.2
unnamed: J105.1, R101.1
unnamed: J107.1, Q101.1, R106.1
unnamed: JA101.SH, JB101.SH, R109.2, R110.2
unnamed: Q101.3, R107.2
unnamed: R1109.1, R1110.2, U1102.4
unnamed: R1110.1, R1111.1, U1102.1
unnamed: U1101.8, U1102.3
Serial_CLK: J109.1, U101.41
Serial_MISO: J108.1, R1203.1, T1201.4, TP101.1, U101.37
Serial_MOSI: J109.2, U101.40
Serial_~CS: J108.2, R1204.2, T1201.6, TP102.1, U101.36
V_Ref1: C101.1, U101.30
V_Ref2: C102.1, R1101.2, R1102.2, R1103.2, R1104.2, R1105.2, R1106.2, R1107.2, R1108.2, U101.31
V_Reg: C1109.2, C1110.1, C1301.2, J101.1, J102.1, J106.1, J1101.1, J1102.1, J1103.1, J1104.1, J1301.1, J1302.1, J1303.1, J1304.1, R101.2, R104.2, R105.2, R111.1, U101.32, U1101.13, U1102.6, U1301.8
WDT: J105.2, U101.42
isoSPI+_OUT: R1201.1, T1201.1, TP103.1, U101.39
isoSPI-_OUT: R1202.2, T1201.3, TP104.1, U101.38
